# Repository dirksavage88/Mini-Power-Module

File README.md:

# Mini-Power-Module
Board and Schematic files for the Mini switching DC-DC Power Module

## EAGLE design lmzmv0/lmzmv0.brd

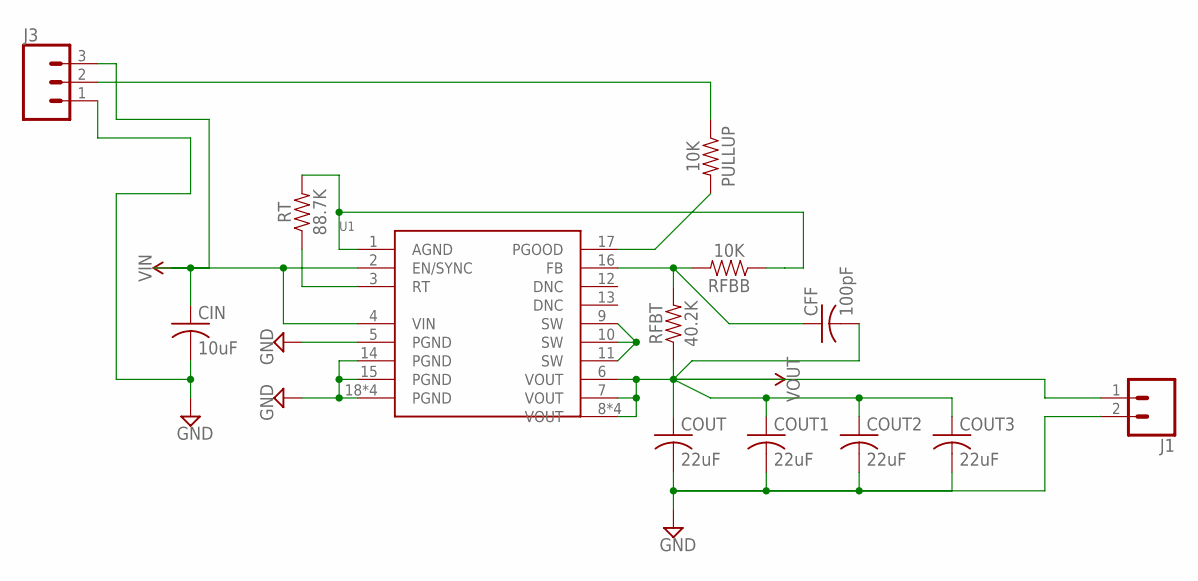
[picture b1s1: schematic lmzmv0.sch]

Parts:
CFF: 100pF; C0603; MPN CC0603JRNPO9BN101
CIN: 10uF; C0603; MPN LMK107BJ106MALTD
COUT, COUT1, COUT2, COUT3: 22uF; C0603; MPN F980G226MMA
J1: CONN_02; 1X02
J3: CONN_031X03_NO_SILK; 1X03_NO_SILK
PULLUP: 10K; 0603; MPN RC0603FR-0710KL
RFBB: 10K; 0603; MPN RC0603FR-0710KL
RFBT: 40.2K; 0603; MPN MC0603SAF4022T5E
RT: 88.7K; 0603; MPN ERJ-S03D8872V
U1: LMZM_MODULEQFN18TI; QFN-18; MPN LMZM33603RLRR

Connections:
AGND: RFBB.1, RT.2, U1.1 (AGND)
FB: CFF.1, RFBB.2, RFBT.2, U1.16 (FB)
GND: CIN.2, COUT.2, COUT1.2, COUT2.2, COUT3.2, J1.2, J3.1, U1.5 (PGND), U1.14 (PGND), U1.15 (PGND), U1.18 (PGND), U1.W (PGND), U1.W1 (PGND), U1.W2 (PGND)
PGOOD: PULLUP.2, U1.17 (PGOOD)
RT: RT.1, U1.3 (RT)
SW: U1.9 (SW), U1.10 (SW), U1.11 (SW)
TPGOOD: J3.2, PULLUP.1
VIN: CIN.1, J3.3, U1.2 (EN/SYNC), U1.4 (VIN)
VOUT: CFF.2, COUT.1, COUT1.1, COUT2.1, COUT3.1, J1.1, RFBT.1, U1.6 (VOUT), U1.7 (VOUT), U1.8 (VOUT), U1.X (VOUT), U1.X1 (VOUT), U1.X2 (VOUT)

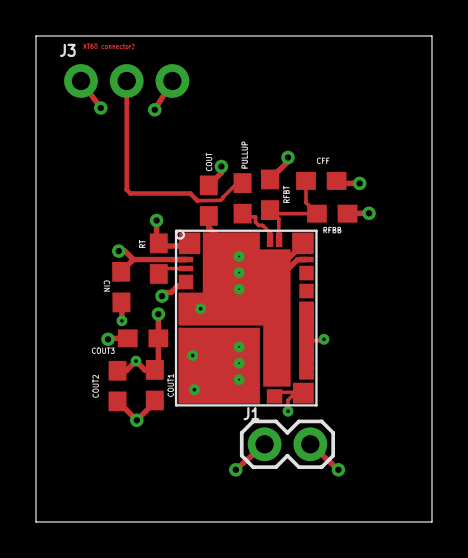
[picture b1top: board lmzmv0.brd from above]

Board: 4 copper layers, 22.0 x 27.0 mm, 13 parts (0 on the bottom side), 9 nets.

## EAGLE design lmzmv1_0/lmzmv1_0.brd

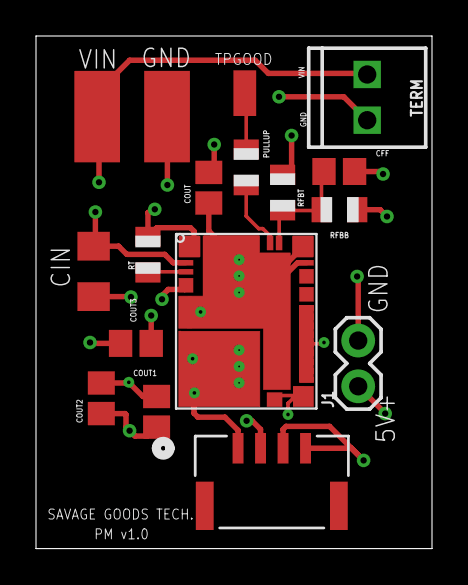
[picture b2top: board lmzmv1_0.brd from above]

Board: 4 copper layers, 22.0 x 28.5 mm, 17 parts (0 on the bottom side), 9 nets.

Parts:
CFF: 100pF; C0805
CIN: C1206
COUT, COUT1, COUT2, COUT3: 22uF; C0805
E$1: CONN_SM04B-GHS-TB_JST
GND: SMD2,54-5,08
J1: 1X02
LMZM33603: QFN-18
PULLUP: 10K; R0805
RFBB: 10K; R0805
RFBT: 40.2K; R0805
RT: 88.7K; R0805
TERM: 1X02_2.54_SCREWTERM
TPGOOD: SMD1,27-2,54
VIN: SMD2,54-5,08

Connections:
AGND: LMZM33603.1, RFBB.1, RT.2
FB: CFF.1, LMZM33603.16, RFBB.2, RFBT.2
GND: CIN.1, COUT.2, COUT1.2, COUT2.2, COUT3.2, E$1.3, E$1.4, GND.1, J1.2, LMZM33603.5, LMZM33603.14, LMZM33603.15, LMZM33603.18, LMZM33603.W, LMZM33603.W1, LMZM33603.W2, TERM.P2
PGOOD: LMZM33603.17, PULLUP.2
RT: LMZM33603.3, RT.1
SW: LMZM33603.9, LMZM33603.10, LMZM33603.11
TPGOOD: PULLUP.1, TPGOOD.1
VIN: CIN.2, LMZM33603.2, LMZM33603.4, TERM.P1, VIN.1
VOUT: CFF.2, COUT.1, COUT1.1, COUT2.1, COUT3.1, E$1.1, E$1.2, J1.1, LMZM33603.6, LMZM33603.7, LMZM33603.8, LMZM33603.X, LMZM33603.X1, LMZM33603.X2, RFBT.1

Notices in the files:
parts and their libraries:
SparkFun-Resistors: Licensing: Creative Commons ShareAlike 4.0 International - https://creativecommons.org/licenses/by-sa/4.0
